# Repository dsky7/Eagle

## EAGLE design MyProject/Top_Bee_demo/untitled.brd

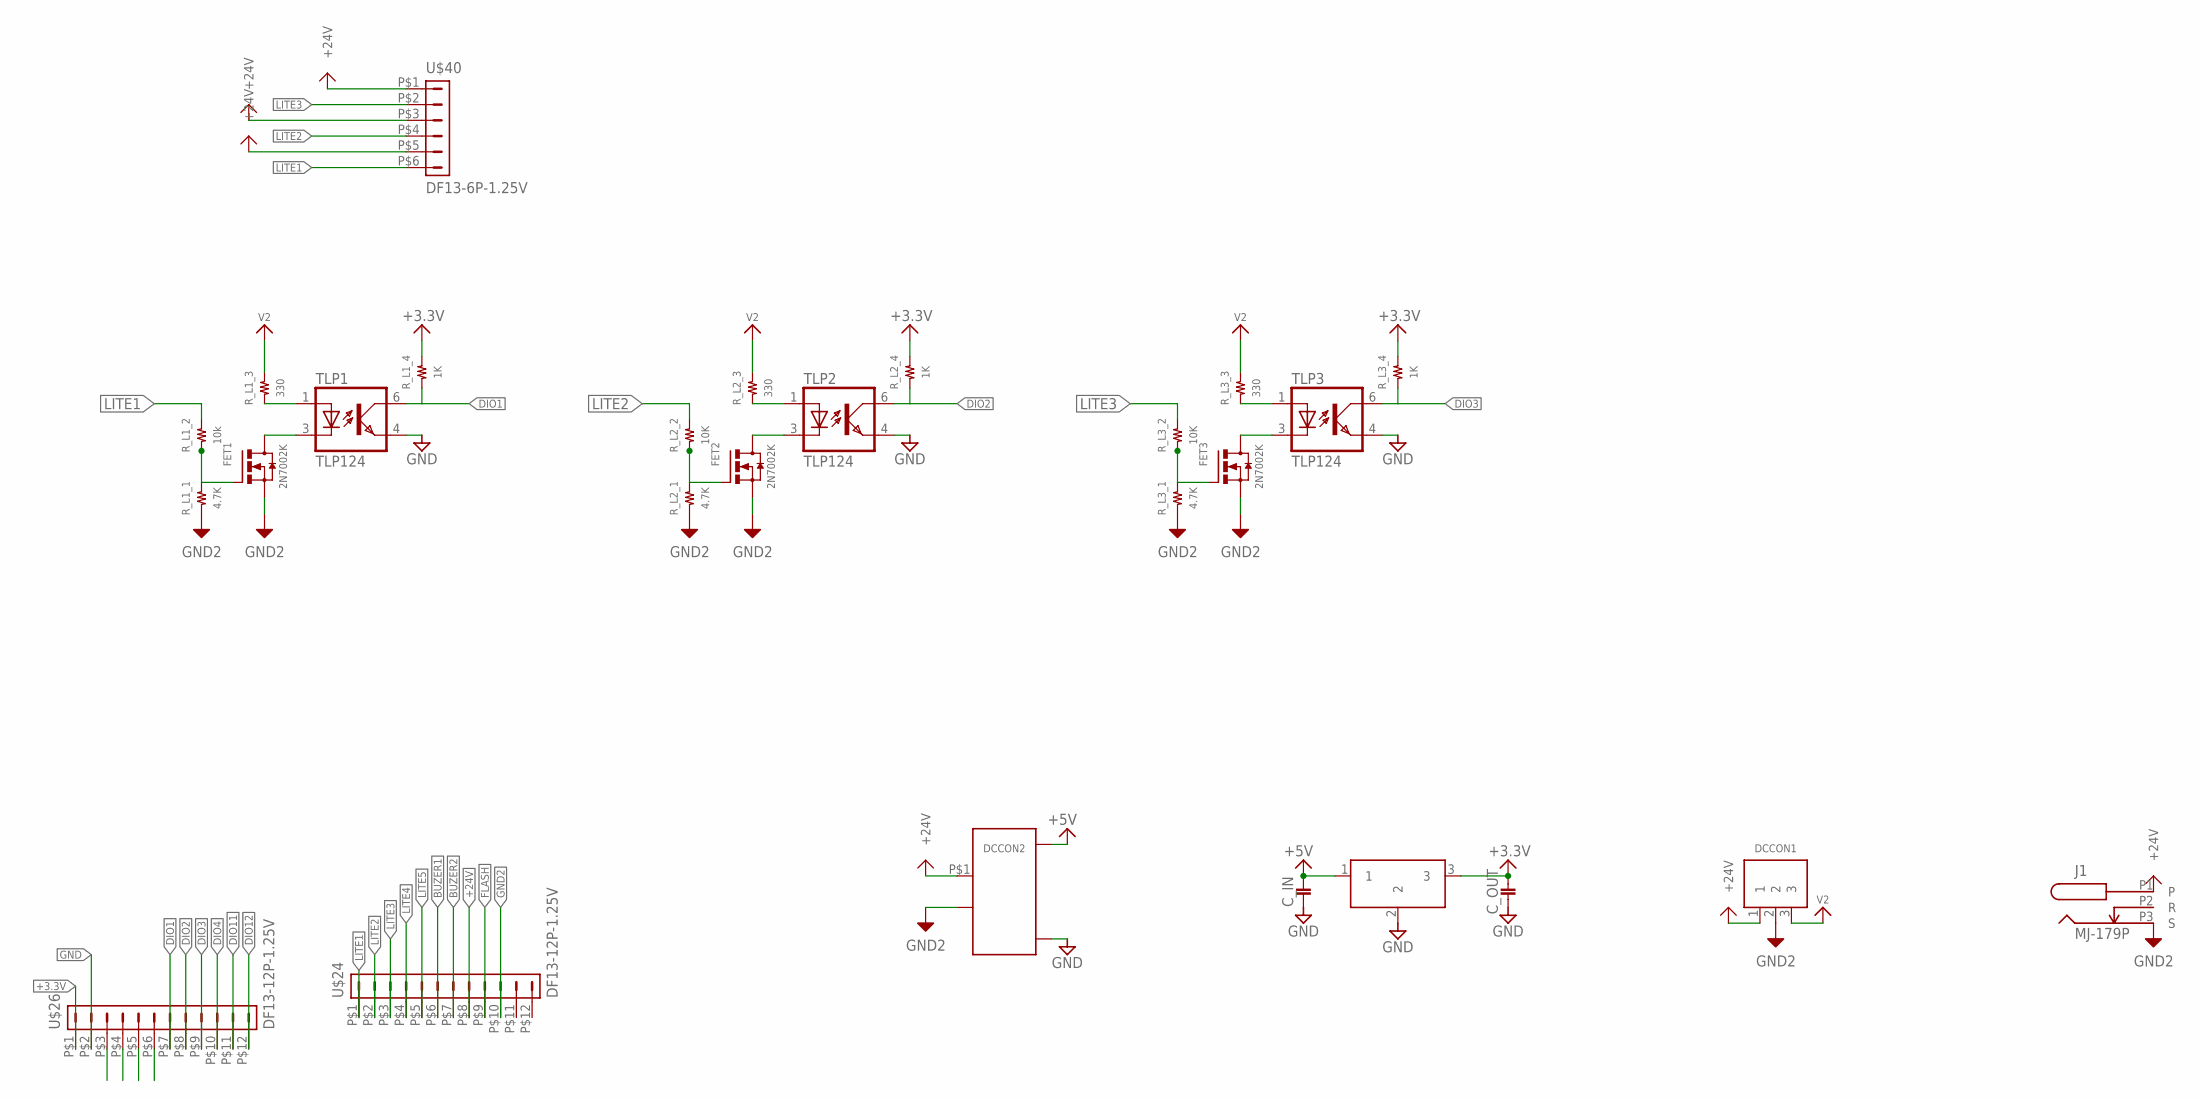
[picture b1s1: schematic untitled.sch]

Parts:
C_IN: 1608
C_OUT: 1608
DCCON1: Ｒ－７８Ｅ５．０
DCCON2: MAU100; MAU
FET1, FET2, FET3: 2N7002K; SOT23
J1: MJ-179P
REGULATOR: NJM2845; TO252
R_L1_1, R_L2_1, R_L3_1: 4.7K; 1608
R_L1_2: 10k; 1608
R_L1_3, R_L2_3, R_L3_3: 330; 1608
R_L1_4, R_L2_4, R_L3_4: 1K; 1608
R_L2_2, R_L3_2: 10K; 1608
TLP1, TLP2, TLP3: TLP124; 11−4C1
U$24, U$26: DF13-12P-1.25V; DF13C-12P-1.25V
U$40: DF13-6P-1.25V; DF13C-6P-1.25V

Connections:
2N7002K: FET1.1 (G), R_L1_1.2, R_L1_2.1
+3.3V: C_OUT.P$1 (1), REGULATOR.3, R_L1_4.2, R_L2_4.2, R_L3_4.2, U$26.P$1 (1)
+5V: C_IN.P$1 (1), DCCON2.P$3 (VO+), REGULATOR.1
+24V: DCCON1.1, DCCON2.P$1 (VIN+), J1.P1, U$24.P$8 (8), U$40.P$1 (1), U$40.P$3 (3), U$40.P$5 (5)
BUZER1: U$24.P$6 (6)
BUZER2: U$24.P$7 (7)
DIO1: R_L1_4.1, TLP1.6 (COL), U$26.P$7 (7)
DIO2: R_L2_4.1, TLP2.6 (COL), U$26.P$8 (8)
DIO3: R_L3_4.1, TLP3.6 (COL), U$26.P$9 (9)
DIO4: U$26.P$10 (10)
DIO11: U$26.P$11 (11)
DIO12: U$26.P$12 (12)
FLASH: U$24.P$9 (9)
GND: C_IN.P$2 (2), C_OUT.P$2 (2), DCCON2.P$5 (VO-), REGULATOR.2, TLP1.4 (EMIT), TLP2.4 (EMIT), TLP3.4 (EMIT), U$26.P$2 (2)
GND2: DCCON1.2, DCCON2.P$2 (VIN-), FET1.2 (S), FET2.2 (S), FET3.2 (S), J1.P3 (S), R_L1_1.1, R_L2_1.1, R_L3_1.1, U$24.P$10 (10)
LITE1: R_L1_2.2, U$24.P$1 (1), U$40.P$6 (6)
LITE2: R_L2_2.2, U$24.P$2 (2), U$40.P$4 (4)
LITE3: R_L3_2.2, U$24.P$3 (3), U$40.P$2 (2)
LITE4: U$24.P$4 (4)
LITE5: U$24.P$5 (5)
unnamed: FET2.3 (D), TLP2.3 (C)
unnamed: FET1.3 (D), TLP1.3 (C)
unnamed: R_L1_3.1, TLP1.1 (A)
unnamed: R_L2_3.1, TLP2.1 (A)
unnamed: FET2.1 (G), R_L2_1.2, R_L2_2.1
unnamed: FET3.3 (D), TLP3.3 (C)
unnamed: R_L3_3.1, TLP3.1 (A)
unnamed: FET3.1 (G), R_L3_1.2, R_L3_2.1
V2: DCCON1.3, R_L1_3.2, R_L2_3.2, R_L3_3.2

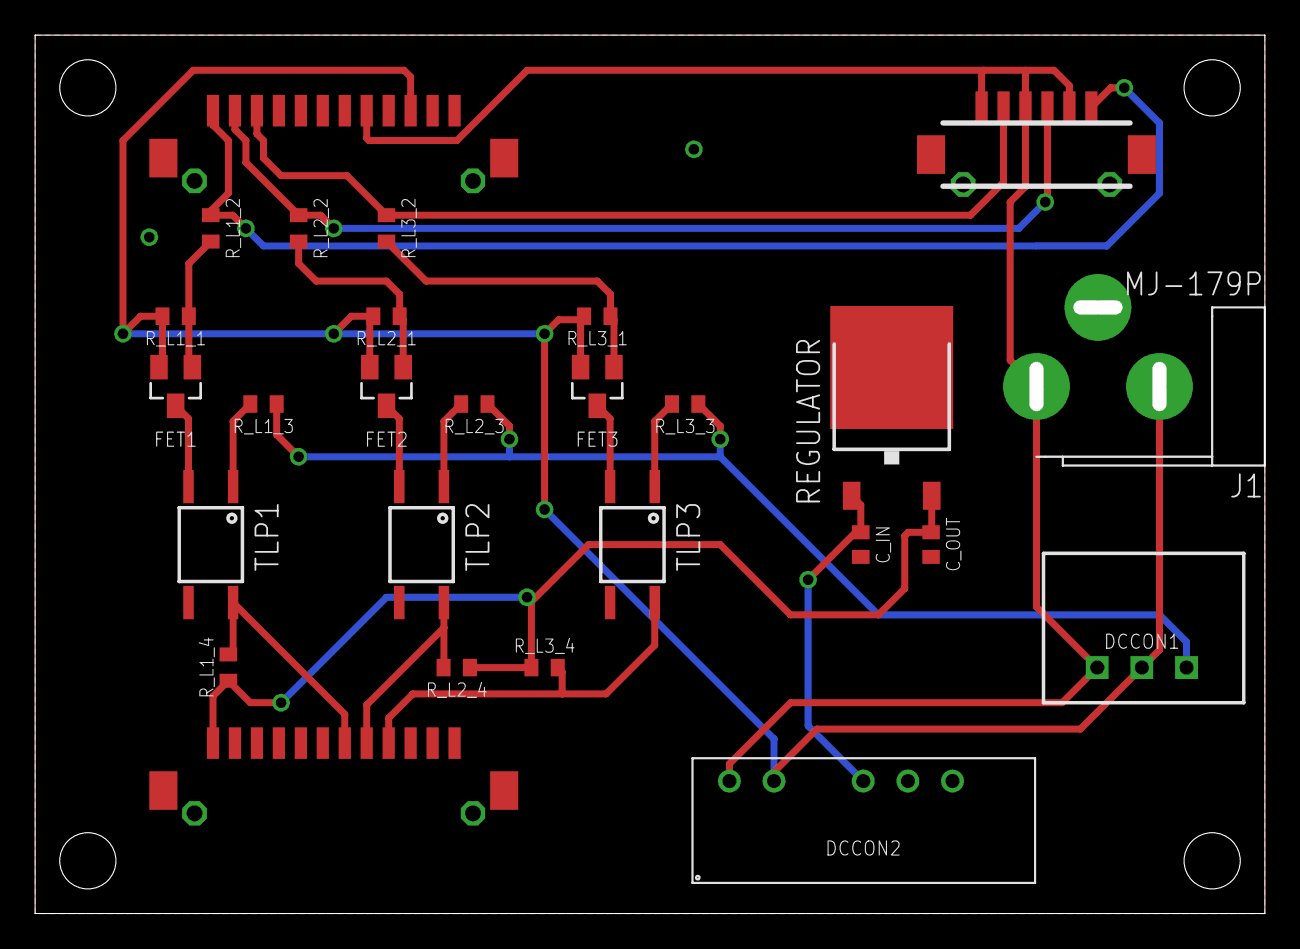
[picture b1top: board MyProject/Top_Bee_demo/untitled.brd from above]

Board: 2 copper layers, 70.0 x 50.0 mm, 27 parts (0 on the bottom side), 21 nets.

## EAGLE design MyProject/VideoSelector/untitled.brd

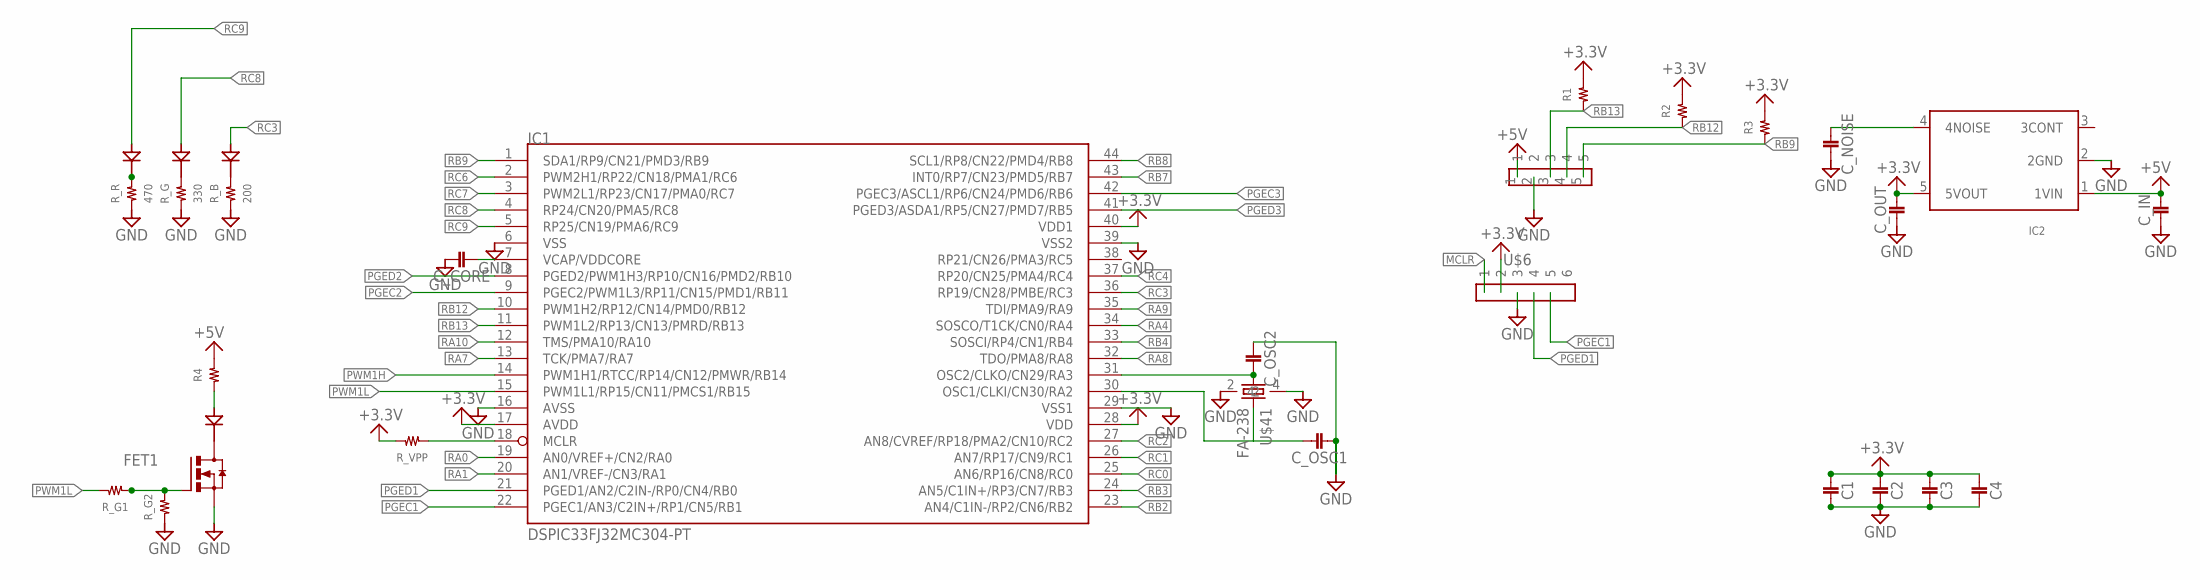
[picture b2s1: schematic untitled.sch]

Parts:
B: CHIPLED; 1608
C1, C2, C3, C4: 1608
C_CORE: 2012
C_IN: 1608
C_NOISE: 1608
C_OSC1, C_OSC2: 1608
C_OUT: 1608
FET1: ＩＲＬＭＬ６３４４; SOT23
G: CHIPLED; 1608
IC1: DSPIC33FJ32MC304-PT; TQFP44
IC2: TAR5SB; SSOP5-P-0.95
IR: 5MMLED; 5MM
R: CHIPLED; 1608
R1, R2, R3, R4: RESISTOR__SMD; 1608
R_B: 200; 1608
R_G: 330; 1608
R_G1, R_G2: RESISTOR__SMD; 1608
R_R: 470; 1608
R_VPP: RESISTOR__SMD; 1608
U$6: PIN_HEADER_6
U$8: PIN_HEADER_5
U$41: FA-238

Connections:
+3.3V: C1.P$2 (2), C2.P$2 (2), C3.P$2 (2), C4.P$2 (2), C_OUT.P$1 (1), IC1.17 (AVDD), IC1.28 (VDD), IC1.40 (VDD1), IC2.5 (5VOUT), R1.2, R2.2, R3.2, R_VPP.2, U$6.2
+5V: C_IN.P$1 (1), IC2.1 (1VIN), R4.2, U$8.1
GND: C1.P$1 (1), C2.P$1 (1), C3.P$1 (1), C4.P$1 (1), C_CORE.1, C_IN.P$2 (2), C_NOISE.P$1 (1), C_OSC1.P$2 (2), C_OSC2.P$2 (2), C_OUT.P$2 (2), FET1.2 (S), IC1.6 (VSS), IC1.16 (AVSS), IC1.29 (VSS1), IC1.39 (VSS2), IC2.2 (2GND), R_B.1, R_G.1, R_G2.1, R_R.1, U$6.3, U$8.2, U$41.2, U$41.4
IC2: C_NOISE.P$2 (2), IC2.4 (4NOISE)
MCLR: IC1.18 (MCLR), R_VPP.1, U$6.1
unnamed: FET1.3 (D), IR.K
unnamed: R.2 (K), R_R.2
unnamed: G.2 (K), R_G.2
unnamed: B.2 (K), R_B.2
unnamed: IR.A, R4.1
unnamed: C_OSC2.P$1 (1), IC1.31 (OSC2/CLKO/CN29/RA3), U$41.1
unnamed: FET1.1 (G), R_G1.1, R_G2.2
unnamed: C_OSC1.P$1 (1), IC1.30 (OSC1/CLKI/CN30/RA2), U$41.3
PGEC1: IC1.22 (PGEC1/AN3/C2IN+/RP1/CN5/RB1), U$6.5
PGEC2: IC1.9 (PGEC2/PWM1L3/RP11/CN15/PMD1/RB11)
PGEC3: IC1.42 (PGEC3/ASCL1/RP6/CN24/PMD6/RB6)
PGED1: IC1.21 (PGED1/AN2/C2IN-/RP0/CN4/RB0), U$6.4
PGED2: IC1.8 (PGED2/PWM1H3/RP10/CN16/PMD2/RB10)
PGED3: IC1.41 (PGED3/ASDA1/RP5/CN27/PMD7/RB5)
PWM1H: IC1.14 (PWM1H1/RTCC/RP14/CN12/PMWR/RB14)
PWM1L: IC1.15 (PWM1L1/RP15/CN11/PMCS1/RB15), R_G1.2
RA0: IC1.19 (AN0/VREF+/CN2/RA0)
RA1: IC1.20 (AN1/VREF-/CN3/RA1)
RA4: IC1.34 (SOSCO/T1CK/CN0/RA4)
RA7: IC1.13 (TCK/PMA7/RA7)
RA8: IC1.32 (TDO/PMA8/RA8)
RA9: IC1.35 (TDI/PMA9/RA9)
RA10: IC1.12 (TMS/PMA10/RA10)
RB2: IC1.23 (AN4/C1IN-/RP2/CN6/RB2)
RB3: IC1.24 (AN5/C1IN+/RP3/CN7/RB3)
RB4: IC1.33 (SOSCI/RP4/CN1/RB4)
RB7: IC1.43 (INT0/RP7/CN23/PMD5/RB7)
RB8: IC1.44 (SCL1/RP8/CN22/PMD4/RB8)
RB9: IC1.1 (SDA1/RP9/CN21/PMD3/RB9), R3.1, U$8.5
RB12: IC1.10 (PWM1H2/RP12/CN14/PMD0/RB12), R2.1, U$8.4
RB13: IC1.11 (PWM1L2/RP13/CN13/PMRD/RB13), R1.1, U$8.3
RC0: IC1.25 (AN6/RP16/CN8/RC0)
RC1: IC1.26 (AN7/RP17/CN9/RC1)
RC2: IC1.27 (AN8/CVREF/RP18/PMA2/CN10/RC2)
RC3: B.1 (A), IC1.36 (RP19/CN28/PMBE/RC3)
RC4: IC1.37 (RP20/CN25/PMA4/RC4)
RC6: IC1.2 (PWM2H1/RP22/CN18/PMA1/RC6)
RC7: IC1.3 (PWM2L1/RP23/CN17/PMA0/RC7)
RC8: G.1 (A), IC1.4 (RP24/CN20/PMA5/RC8)
RC9: IC1.5 (RP25/CN19/PMA6/RC9), R.1 (A)
VCAP/VDDCORE: C_CORE.2, IC1.7 (VCAP/VDDCORE)

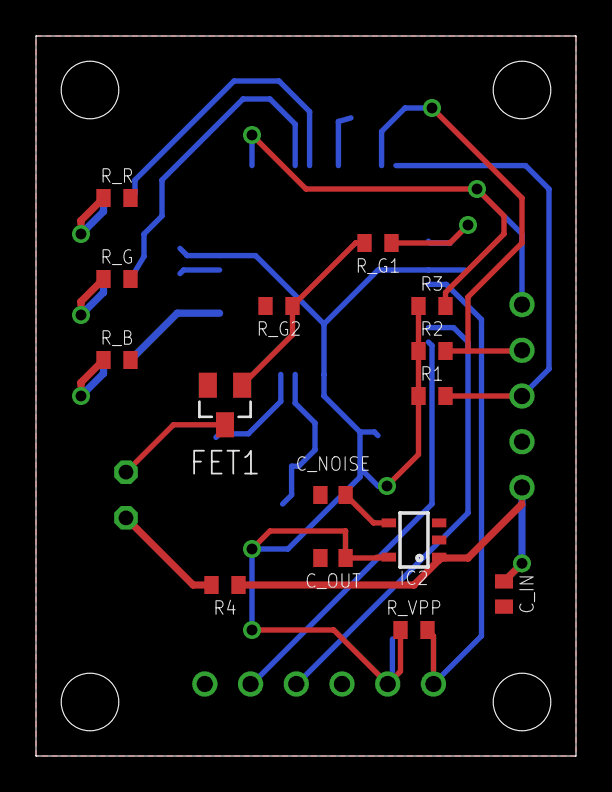
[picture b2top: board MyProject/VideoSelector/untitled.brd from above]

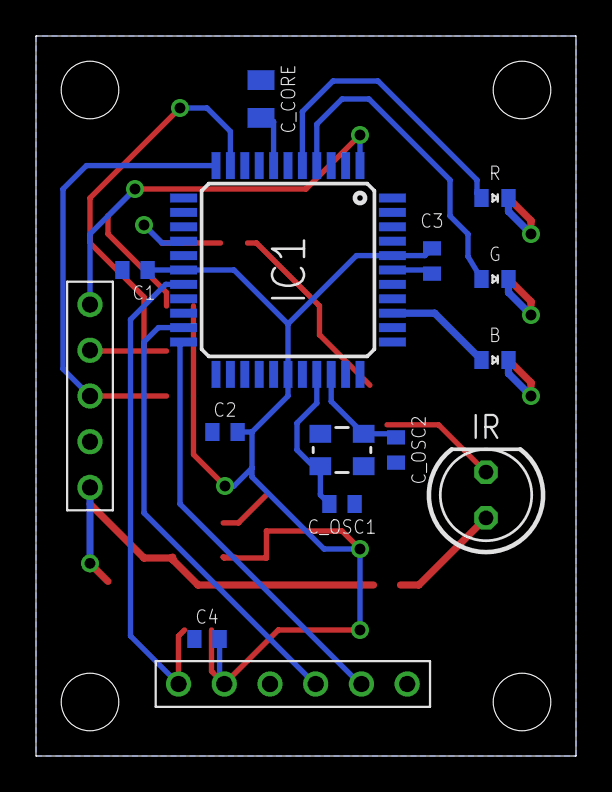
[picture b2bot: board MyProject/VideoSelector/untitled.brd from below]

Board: 2 copper layers, 30.0 x 40.0 mm, 30 parts (15 on the bottom side), 23 nets.

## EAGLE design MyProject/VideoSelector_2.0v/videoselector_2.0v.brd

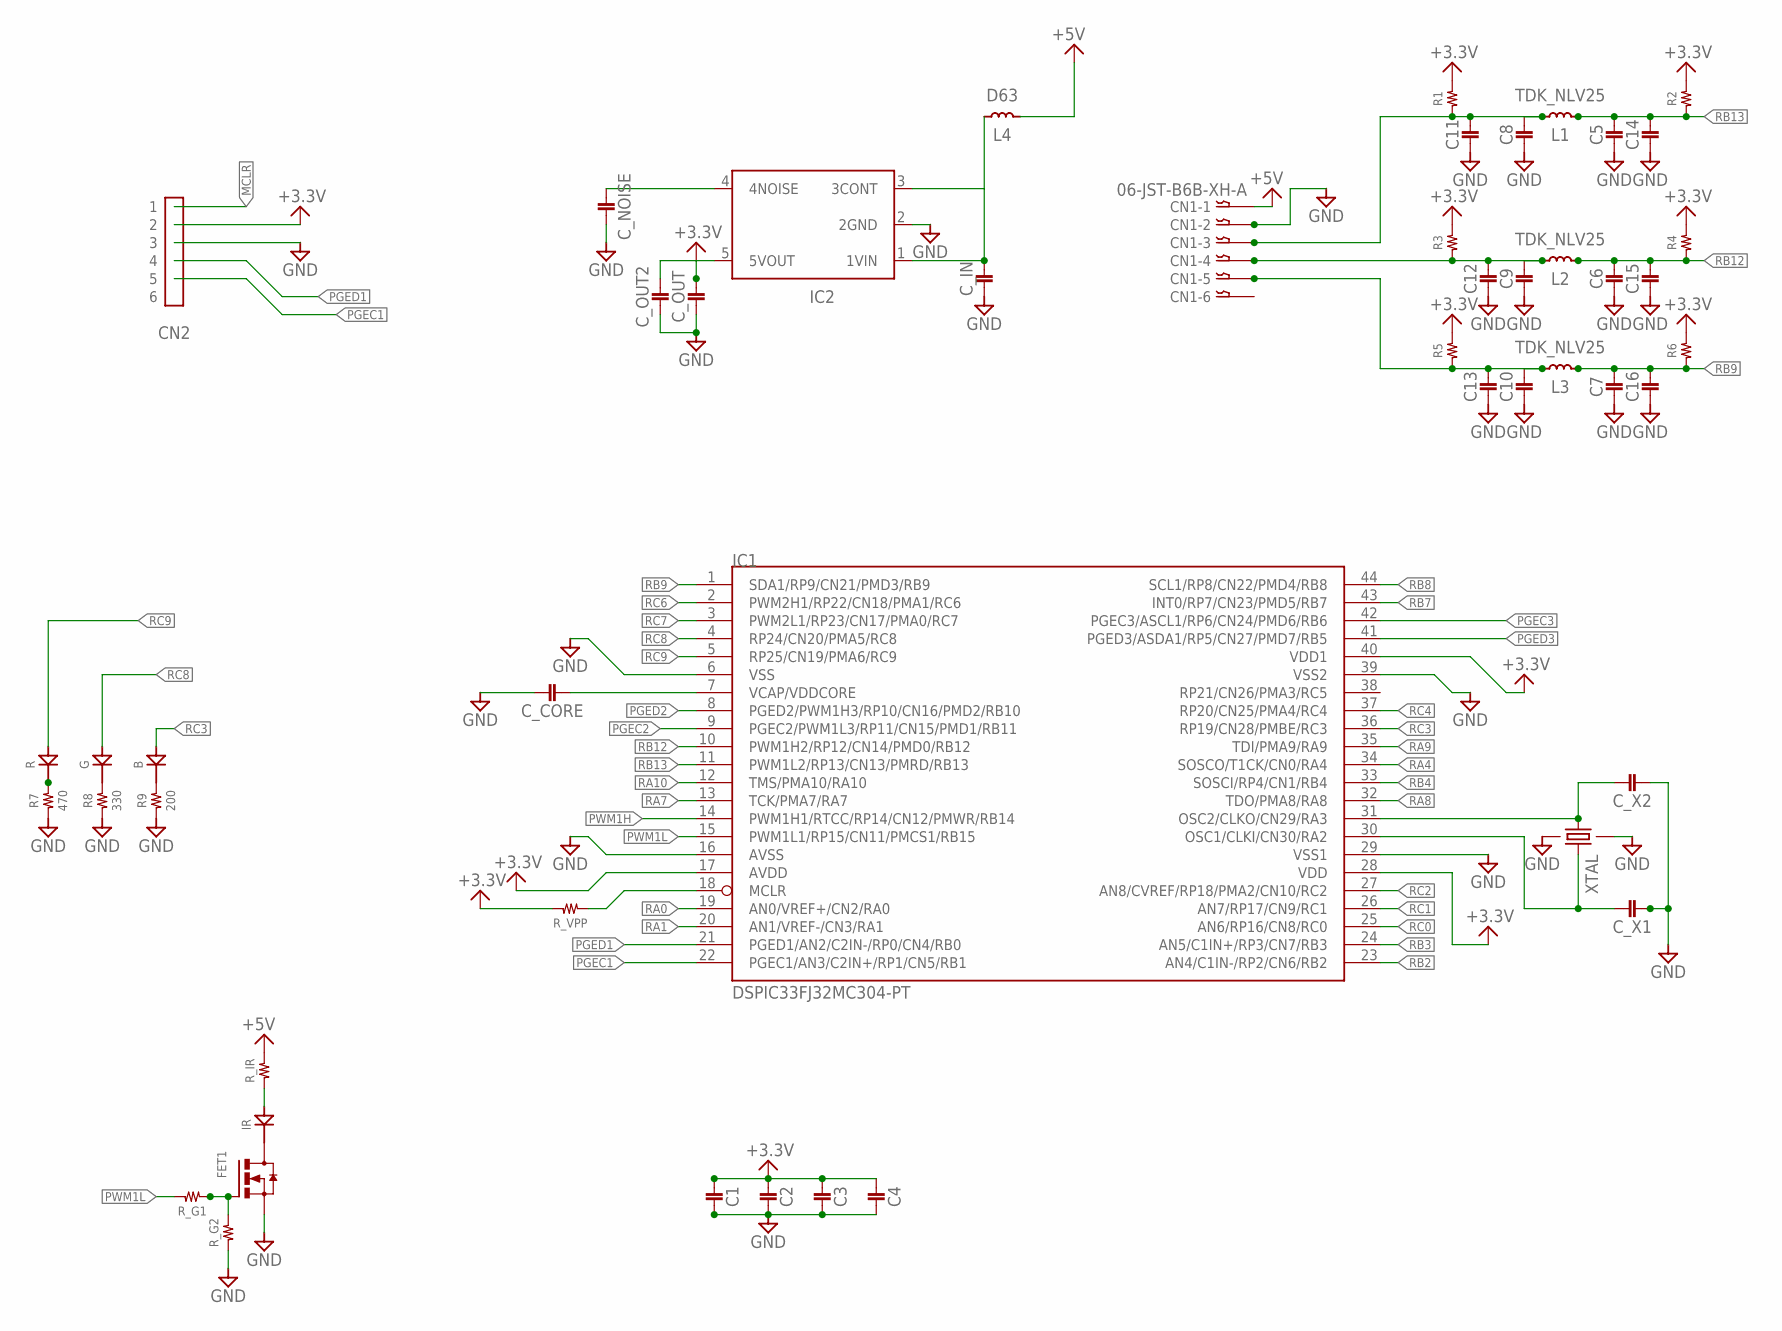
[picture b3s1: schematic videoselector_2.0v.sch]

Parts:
B: CHIPLED; 1608
C1, C2, C3, C4, C5, C6, C7, C8, C9, C10: 1608
C11, C12, C13, C14, C15, C16: 3225
CN1: 06-JST-B6B-XH-A; B6B-XH
CN2: PIN_HEADER_6
C_CORE: 2012
C_IN: 1608
C_NOISE: 1608
C_OUT: 1608
C_OUT2: 2012
C_X1, C_X2: 1608
FET1: ＩＲＬＭＬ６３４４; SOT23
G: CHIPLED; 1608
IC1: DSPIC33FJ32MC304-PT; TQFP44
IC2: TAR5SB; SSOP5-P-0.95
IR: 5MMLED; 5MM
L1, L2, L3: TDK_NLV25; TDK_NLV
L4: D63; TOKO
R: CHIPLED; 1608
R1, R2, R3, R4, R5, R6: RESISTOR__SMD; 1608
R7: 470; 1608
R8: 330; 1608
R9: 200; 1608
R_G1, R_G2: RESISTOR__SMD; 1608
R_IR: RESISTOR__SMD; 1608
R_VPP: RESISTOR__SMD; 1608
XTAL: FA-238

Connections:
+3.3V: C1.P$2 (2), C2.P$2 (2), C3.P$2 (2), C4.P$2 (2), CN2.2, C_OUT.P$1 (1), C_OUT2.1, IC1.17 (AVDD), IC1.28 (VDD), IC1.40 (VDD1), IC2.5 (5VOUT), R1.2, R2.2, R3.2, R4.2, R5.2, R6.2, R_VPP.2
+5V: CN1.P$1, L4.2, R_IR.2
GND: C1.P$1 (1), C2.P$1 (1), C3.P$1 (1), C4.P$1 (1), C5.P$2 (2), C6.P$2 (2), C7.P$2 (2), C8.P$2 (2), C9.P$2 (2), C10.P$2 (2), C11.P$2 (2), C12.P$2 (2), C13.P$2 (2), C14.P$2 (2), C15.P$2 (2), C16.P$2 (2), CN1.P$2, CN2.3, C_CORE.1, C_IN.P$2 (2), C_NOISE.P$1 (1), C_OUT.P$2 (2), C_OUT2.2, C_X1.P$2 (2), C_X2.P$2 (2), FET1.2 (S), IC1.6 (VSS), IC1.16 (AVSS), IC1.29 (VSS1), IC1.39 (VSS2), IC2.2 (2GND), R7.1, R8.1, R9.1, R_G2.1, XTAL.2, XTAL.4
IC2: C_NOISE.P$2 (2), IC2.4 (4NOISE)
MCLR: CN2.1, IC1.18 (MCLR), R_VPP.1
unnamed: FET1.3 (D), IR.K
unnamed: R.2 (K), R7.2
unnamed: G.2 (K), R8.2
unnamed: B.2 (K), R9.2
unnamed: IR.A, R_IR.1
unnamed: C8.P$1 (1), C11.P$1 (1), CN1.P$3, L1.P$1 (1), R1.1
unnamed: C9.P$1 (1), C12.P$1 (1), CN1.P$4, L2.P$1 (1), R3.1
unnamed: C_X2.P$1 (1), IC1.31 (OSC2/CLKO/CN29/RA3), XTAL.1
unnamed: FET1.1 (G), R_G1.1, R_G2.2
unnamed: C_X1.P$1 (1), IC1.30 (OSC1/CLKI/CN30/RA2), XTAL.3
unnamed: C10.P$1 (1), C13.P$1 (1), CN1.P$5, L3.P$1 (1), R5.1
unnamed: C_IN.P$1 (1), IC2.1 (1VIN), IC2.3 (3CONT), L4.1
PGEC1: CN2.5, IC1.22 (PGEC1/AN3/C2IN+/RP1/CN5/RB1)
PGEC2: IC1.9 (PGEC2/PWM1L3/RP11/CN15/PMD1/RB11)
PGEC3: IC1.42 (PGEC3/ASCL1/RP6/CN24/PMD6/RB6)
PGED1: CN2.4, IC1.21 (PGED1/AN2/C2IN-/RP0/CN4/RB0)
PGED2: IC1.8 (PGED2/PWM1H3/RP10/CN16/PMD2/RB10)
PGED3: IC1.41 (PGED3/ASDA1/RP5/CN27/PMD7/RB5)
PWM1H: IC1.14 (PWM1H1/RTCC/RP14/CN12/PMWR/RB14)
PWM1L: IC1.15 (PWM1L1/RP15/CN11/PMCS1/RB15), R_G1.2
RA0: IC1.19 (AN0/VREF+/CN2/RA0)
RA1: IC1.20 (AN1/VREF-/CN3/RA1)
RA4: IC1.34 (SOSCO/T1CK/CN0/RA4)
RA7: IC1.13 (TCK/PMA7/RA7)
RA8: IC1.32 (TDO/PMA8/RA8)
RA9: IC1.35 (TDI/PMA9/RA9)
RA10: IC1.12 (TMS/PMA10/RA10)
RB2: IC1.23 (AN4/C1IN-/RP2/CN6/RB2)
RB3: IC1.24 (AN5/C1IN+/RP3/CN7/RB3)
RB4: IC1.33 (SOSCI/RP4/CN1/RB4)
RB7: IC1.43 (INT0/RP7/CN23/PMD5/RB7)
RB8: IC1.44 (SCL1/RP8/CN22/PMD4/RB8)
RB9: C7.P$1 (1), C16.P$1 (1), IC1.1 (SDA1/RP9/CN21/PMD3/RB9), L3.P$2 (2), R6.1
RB12: C6.P$1 (1), C15.P$1 (1), IC1.10 (PWM1H2/RP12/CN14/PMD0/RB12), L2.P$2 (2), R4.1
RB13: C5.P$1 (1), C14.P$1 (1), IC1.11 (PWM1L2/RP13/CN13/PMRD/RB13), L1.P$2 (2), R2.1
RC0: IC1.25 (AN6/RP16/CN8/RC0)
RC1: IC1.26 (AN7/RP17/CN9/RC1)
RC2: IC1.27 (AN8/CVREF/RP18/PMA2/CN10/RC2)
RC3: B.1 (A), IC1.36 (RP19/CN28/PMBE/RC3)
RC4: IC1.37 (RP20/CN25/PMA4/RC4)
RC6: IC1.2 (PWM2H1/RP22/CN18/PMA1/RC6)
RC7: IC1.3 (PWM2L1/RP23/CN17/PMA0/RC7)
RC8: G.1 (A), IC1.4 (RP24/CN20/PMA5/RC8)
RC9: IC1.5 (RP25/CN19/PMA6/RC9), R.1 (A)
VCAP/VDDCORE: C_CORE.2, IC1.7 (VCAP/VDDCORE)

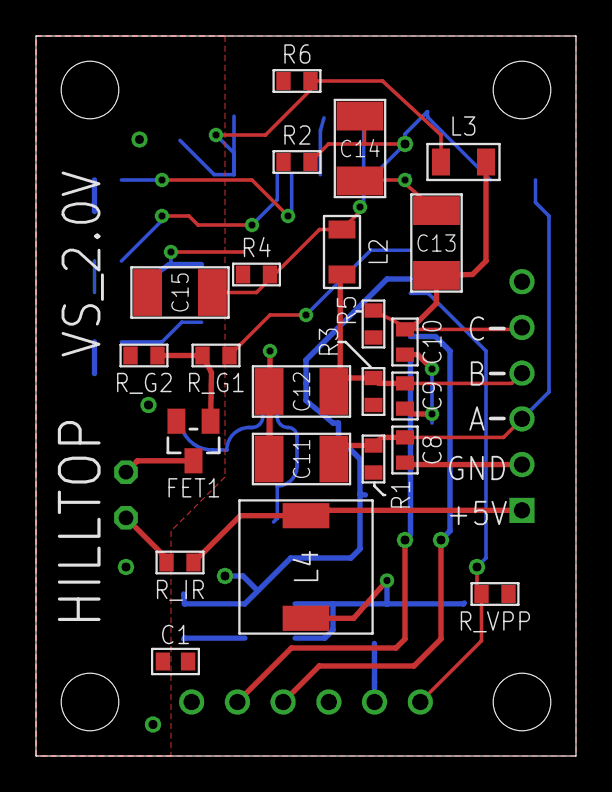
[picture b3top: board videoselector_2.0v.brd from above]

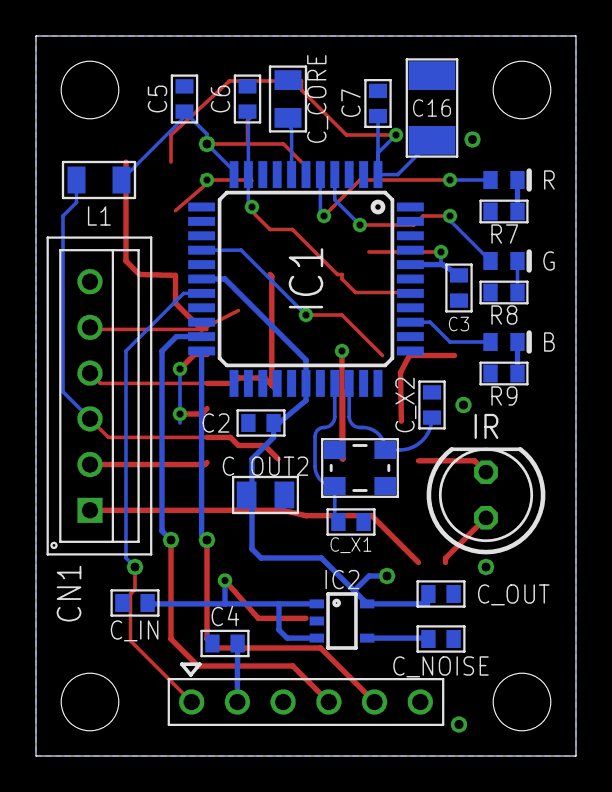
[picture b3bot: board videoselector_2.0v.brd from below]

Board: 2 copper layers, 30.0 x 40.0 mm, 51 parts (27 on the bottom side), 27 nets.

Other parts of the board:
DRILEGEND: DRILEGEND

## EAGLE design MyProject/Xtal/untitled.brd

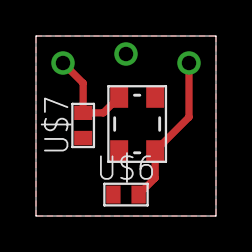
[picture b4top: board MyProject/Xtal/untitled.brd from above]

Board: 2 copper layers, 10.0 x 10.0 mm, 6 parts (0 on the bottom side), 3 nets.

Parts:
U$1: FA-238
U$4, U$5, U$10: CHECK_0.8MM
U$6, U$7: 1608

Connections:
GND: U$1.2, U$1.4, U$6.P$1, U$7.P$1, U$10.P$1
unnamed: U$1.1, U$5.P$1, U$7.P$2
unnamed: U$1.3, U$4.P$1, U$6.P$2

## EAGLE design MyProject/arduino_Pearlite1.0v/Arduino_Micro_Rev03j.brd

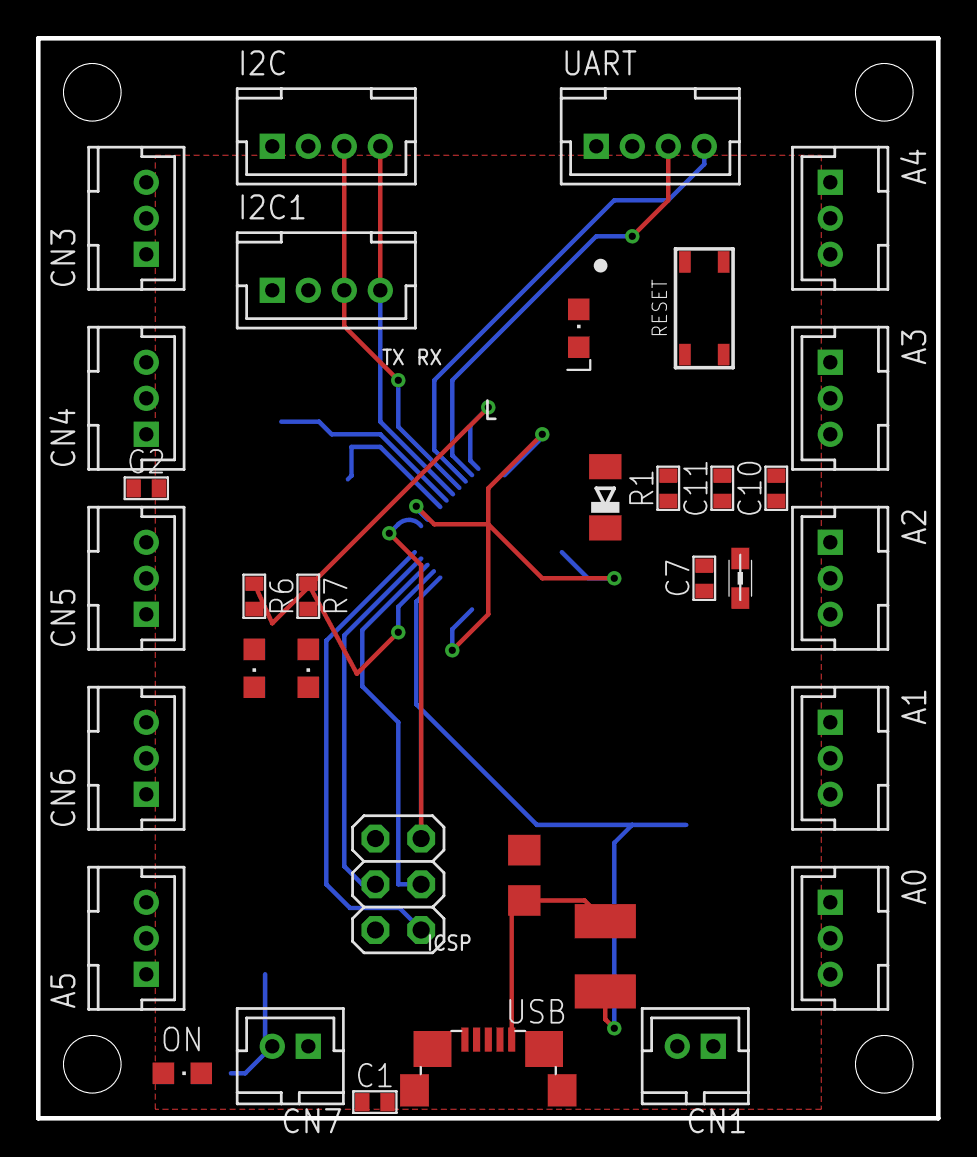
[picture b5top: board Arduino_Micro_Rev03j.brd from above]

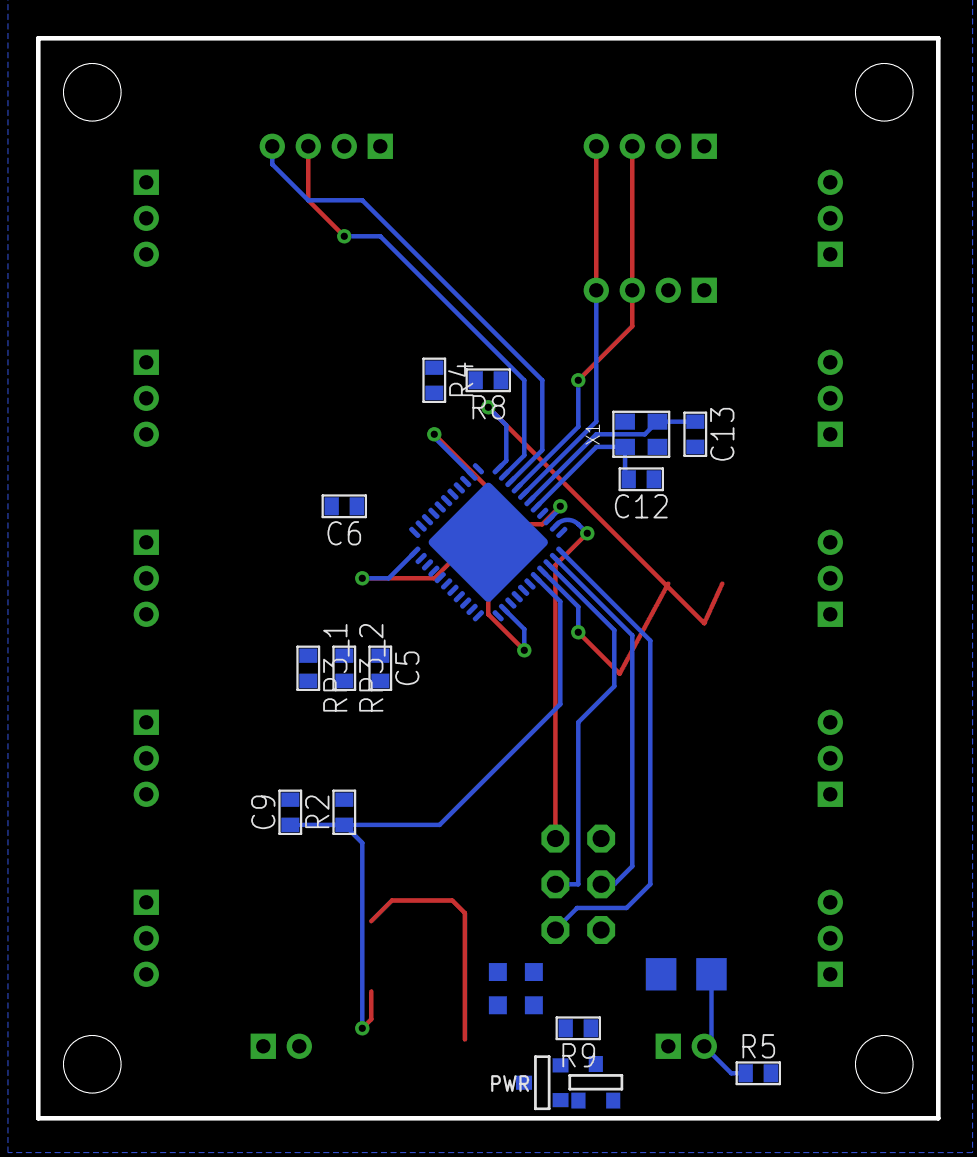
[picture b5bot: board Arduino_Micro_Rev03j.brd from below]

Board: 4 copper layers, 50.0 x 60.0 mm, 53 parts (19 on the bottom side), 41 nets.

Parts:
A0, A1, A2, A3, A4, A5: B3B-PH-K-S
C1, C2, C5, C6, C7, C9, C10, C11, C12, C13: 1608
C3, C14: 3216
CN1, CN7: B2B-PH-K-S
CN3, CN4, CN5, CN6: B3B-PH-K-S
D2: CD1206-S01575; MINIMELF
F1: MF-MSMF050-2 500mA; L1812
I2C, I2C1: B4B-PH-K-S
J4: 3x2M; 2X03
L: green; CHIPLED_0805
L2: MH2029-300Y; 0805
ON: blue; CHIPLED_0805
R1, R2, R4, R5, R6, R7, R8, R9: 1608
RESET: SKRPACE010; SKRP
RP3_1, RP3_2: 1608
RX: yellow; CHIPLED_0805
T1: FDN340P/PMV48XP; SOT-23
T2: PMV48XP; SOT-23
TX: yellow; CHIPLED_0805
U1: ATMEGA32U4-XUMU; QFN44ML7X7
UART: B4B-PH-K-S
USB: MICRO-USB-SHIELD-ZX62R-B-5P; ZX62R-B-5P
X1: X22; SMD_X22
Z1, Z2: CG0603MLC-05E; CT/CN0603

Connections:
+5V: A0.2, A1.2, A2.2, A3.2, A4.2, A5.2, C2.P$1, C3.P$1, C10.P$1, C11.P$1, CN3.2, CN4.2, CN5.2, CN6.2, CN7.2, D2.C, I2C.2, I2C1.2, J4.2, L2.1, R1.2, R5.2, T1.2, T2.3, U1.2, U1.14, U1.24, U1.34, UART.2
+VIN: C1.P$1, T2.2
A0: A0.3, U1.36
A1: A1.3, U1.37
A2: A2.3, U1.38
A3: A3.3, U1.39
A4: A4.3, U1.40
A5: A5.3, U1.41
AREF: C6.P$1, U1.42
AVCC: C7.P$1, L2.2, U1.44
D0/RX: U1.20, UART.4
D1/TX: U1.21, UART.3
D2/SDA: I2C.3, I2C1.3, U1.19
D3/SCL: I2C.4, I2C1.4, U1.18
D4*: CN3.3, U1.25
D6*: CN4.3, U1.27
D+: RP3_2.1, USB.3, Z1.1
D-: RP3_1.1, USB.2, Z2.1
GND: A0.1, A1.1, A2.1, A3.1, A4.1, A5.1, C1.P$2, C2.P$2, C3.P$2, C5.P$2, C6.P$2, C7.P$2, C9.P$2, C10.P$2, C11.P$2, C12.P$1, C13.P$1, C14.P$2, CN3.1, CN4.1, CN5.1, CN6.1, CN7.1, I2C.1, I2C1.1, J4.6, L.C, ON.C, R2.1, R4.1, R9.1, RESET.3, RESET.4, RX.C, TX.C, U1.5, U1.15, U1.23, U1.35, U1.43, U1.EXP, UART.1, USB.5, USB.M1, USB.M2, USB.M3, USB.M4, X1.2, X1.4, Z1.2, Z2.2
HWB: R4.2, U1.33
IO9*: CN5.3, U1.29
IO10*: CN6.3, U1.30
IO13*: R8.2, U1.32
MISO: J4.1, U1.11
MOSI: J4.4, U1.10
unnamed: R7.1, RX.A
unnamed: ON.A, R5.1
unnamed: R6.1, TX.A
unnamed: L.A, R8.1
RD+: RP3_2.2, U1.4
RD-: RP3_1.2, U1.3
RESET: D2.A, J4.5, R1.1, RESET.1, RESET.2, U1.13
RXLED/SS: R7.2, U1.8
SCK: J4.3, U1.9
TXLED: R6.2, U1.22
UCAP: C5.P$1, U1.6
VIN: R9.2, T1.3, T2.1
VUSB: C9.P$1, F1.2, R2.2, T1.1, U1.7
VUSBD: C14.P$1, F1.1, USB.1
XTAL1: C13.P$2, U1.17, X1.3
XTAL2: C12.P$2, U1.16, X1.1

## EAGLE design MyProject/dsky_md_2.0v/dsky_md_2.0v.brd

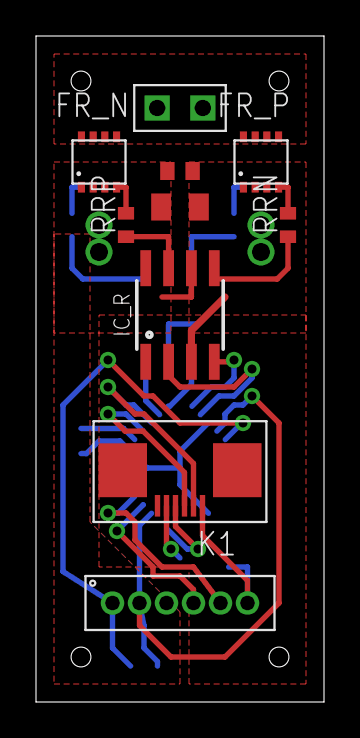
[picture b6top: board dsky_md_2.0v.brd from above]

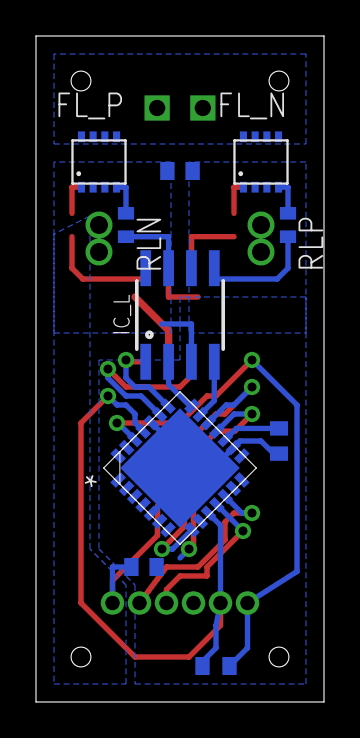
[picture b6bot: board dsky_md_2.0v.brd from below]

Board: 2 copper layers, 16.0 x 37.0 mm, 20 parts (10 on the bottom side), 24 nets.

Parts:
FL_N: ECH84; ECH8
FL_P: ECH83; ECH8
FR_N: ECH84; ECH8
FR_P: ECH83; ECH8
IC_L: TC1427COA; SOIC8
IC_R: TC1427COA; SOIC8
K1: 68710614522
RLN: RESISTOR_SMD_1005; 1005
RLP: RESISTOR_SMD_1005; 1005
RRN: RESISTOR_SMD_1005; 1005
RRP: RESISTOR_SMD_1005; 1005
U$3: PIN_HEADER_2; PIN_HEADER_2S
U$5: DSPIC33EP32MC202; QFN-S28_6X6MC
U$6: PIN_HEADER_HALF_6
U$16, U$17, U$18, U$22, U$25: 1608
U$29: 2012

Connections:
+3.3V: U$5.10, U$5.25, U$6.2, U$22.2
+5V: FL_P.1, FL_P.2, FL_P.3, FR_P.1, FR_P.2, FR_P.3, IC_L.3, IC_R.3, K1.1, U$6.6, U$16.P$1, U$17.P$1, U$18.P$1, U$29.1
GND: FL_N.1, FL_N.2, FL_N.3, FR_N.1, FR_N.2, FR_N.3, IC_L.6, IC_R.6, K1.5, U$5.5, U$5.16, U$5.24, U$5.29, U$6.3, U$16.P$2, U$17.P$2, U$18.P$2, U$25.P$2, U$29.2
M_L: FL_N.5, FL_N.6, FL_N.7, FL_N.8, FL_P.5, FL_P.6, FL_P.7, FL_P.8, U$3.P$1
M_R: FR_N.5, FR_N.6, FR_N.7, FR_N.8, FR_P.5, FR_P.6, FR_P.7, FR_P.8, U$3.P$2
unnamed: FL_P.4, RLN.1
unnamed: FL_N.4, RLP.1
unnamed: IC_L.7, RLN.2
unnamed: FR_P.4, RRN.2
unnamed: IC_L.5, RLP.2
unnamed: IC_R.7, RRP.1
unnamed: U$5.17, U$25.P$1
unnamed: IC_R.5, RRN.1
unnamed: U$5.11, U$6.4
unnamed: U$5.12, U$6.5
unnamed: FR_N.4, RRP.2
P1H: IC_R.4, U$5.22
P1L: IC_R.2, U$5.23
P2H: IC_L.4, U$5.20
P2L: IC_L.2, U$5.21
RB4: K1.4, U$5.8
RB10: K1.3, U$5.18
RB11: K1.2, U$5.19
VPP: U$5.26, U$6.1, U$22.1

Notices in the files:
parts and their libraries:
Wuerth_Elektronik_eiCan_03_ZIF_Connector: Copyright: Würth Elektronik
